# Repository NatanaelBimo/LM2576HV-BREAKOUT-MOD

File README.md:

# LM2576HV Step-Down Voltage Regulator Breakout Board

A breakout board for the LM2576HV switching voltage regulator configured for 12V output.

## Features

- Input voltage: Up to 60V DC
- Fixed 12V output 
- High efficiency step-down (buck) switching regulator
- TO-263-5 package for good thermal performance
- Input and output capacitor filtering
- Standard 0805 and electrolytic capacitors used
- PCB mounting holes

## Specifications

- Input voltage range: 12V to 60V DC
- Output voltage: 12V fixed
- Maximum output current: 3A
- Switching frequency: 52kHz (typical)
- Efficiency: Up to 90%

## Pin Configuration

- VIN: Input voltage (12-60V)
- GND: Ground
- VOUT: 12V regulated output

## Notes

- Input capacitor should be rated for >50V
- Output capacitor should be rated for >16V
- Use adequate cooling/heatsinking at high power levels
- Refer to LM2576 datasheet for detailed specifications

## License

This hardware is open source under the MIT license.

## References

- [LM2576 Datasheet](http://www.ti.com/lit/ds/symlink/lm2576.pdf)

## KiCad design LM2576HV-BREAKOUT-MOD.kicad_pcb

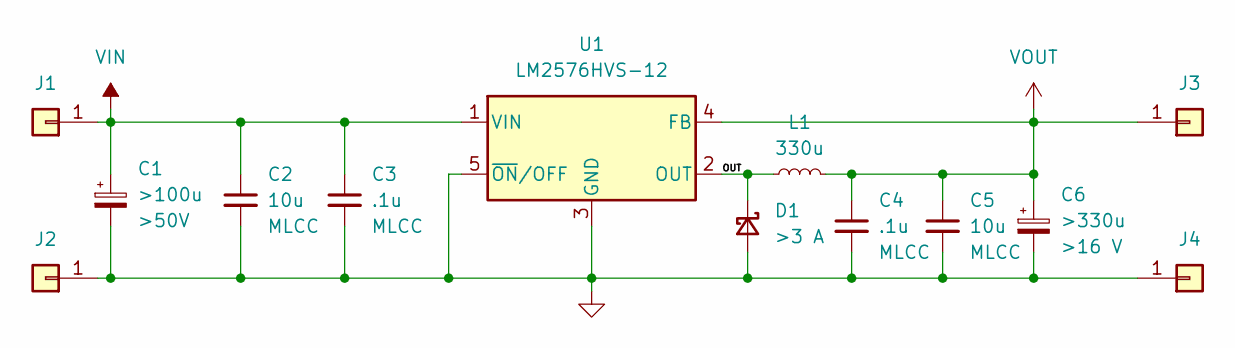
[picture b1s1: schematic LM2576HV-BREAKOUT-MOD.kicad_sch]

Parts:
C1: >100u; CP_Elec_10x10
C2, C5: 10u; C_0805_2012Metric
C3, C4: .1u; C_0805_2012Metric
C6: >330u; CP_Elec_10x10
D1: >3 A; D_SMC
J1, J2, J3, J4: Conn_01x01; PinHeader_1x01_P2.54mm_Vertical
L1: 330u; L_SXN_SMDRI127
U1: LM2576HVS-12; TO-263-5_TabPin3

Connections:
/OUT: D1.1 (K), L1.1, U1.2 (OUT)
GND: C1.2, C2.2, C3.2, C4.2, C5.2, C6.2, D1.2 (A), J2.1, J4.1, U1.3 (GND), U1.5 (~ON/OFF)
VIN: C1.1, C2.1, C3.1, J1.1, U1.1 (VIN)
VOUT: C4.1, C5.1, C6.1, J3.1, L1.2, U1.4 (FB)

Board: 2 copper layers, 13 parts (0 on the bottom side), 4 nets, no tracks yet.

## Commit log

2025-11-08 Update LM2576HV Breakout Mod to use LM2576HVS-12
    - Removed unused potentiometer symbol and associated properties from schematic.
    - Updated LM2576HVS-ADJ references to LM2576HVS-12 in schematic, including properties and symbols.
    - Adjusted junction and wire positions for better layout.
    - Removed redundant wires and no-connects to clean up the schematic.
    - Updated connector positions for better alignment.
2025-11-08 Add LICENSE and README files for project documentation
2025-11-08 Add MIT License to project documentation
2025-11-08 Remove LICENSE.md file from the project
2025-11-08 Add view.png image file to the project
